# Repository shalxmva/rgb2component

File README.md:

# rgb2component
Cheap RGB to component transcoder based on dekkit schemati  https://github.com/dekkit/RGB-to-Component-Transcoder

   -The main goal for this project is to build a tiny board.
   -Next revisions will replace through hole for smd components

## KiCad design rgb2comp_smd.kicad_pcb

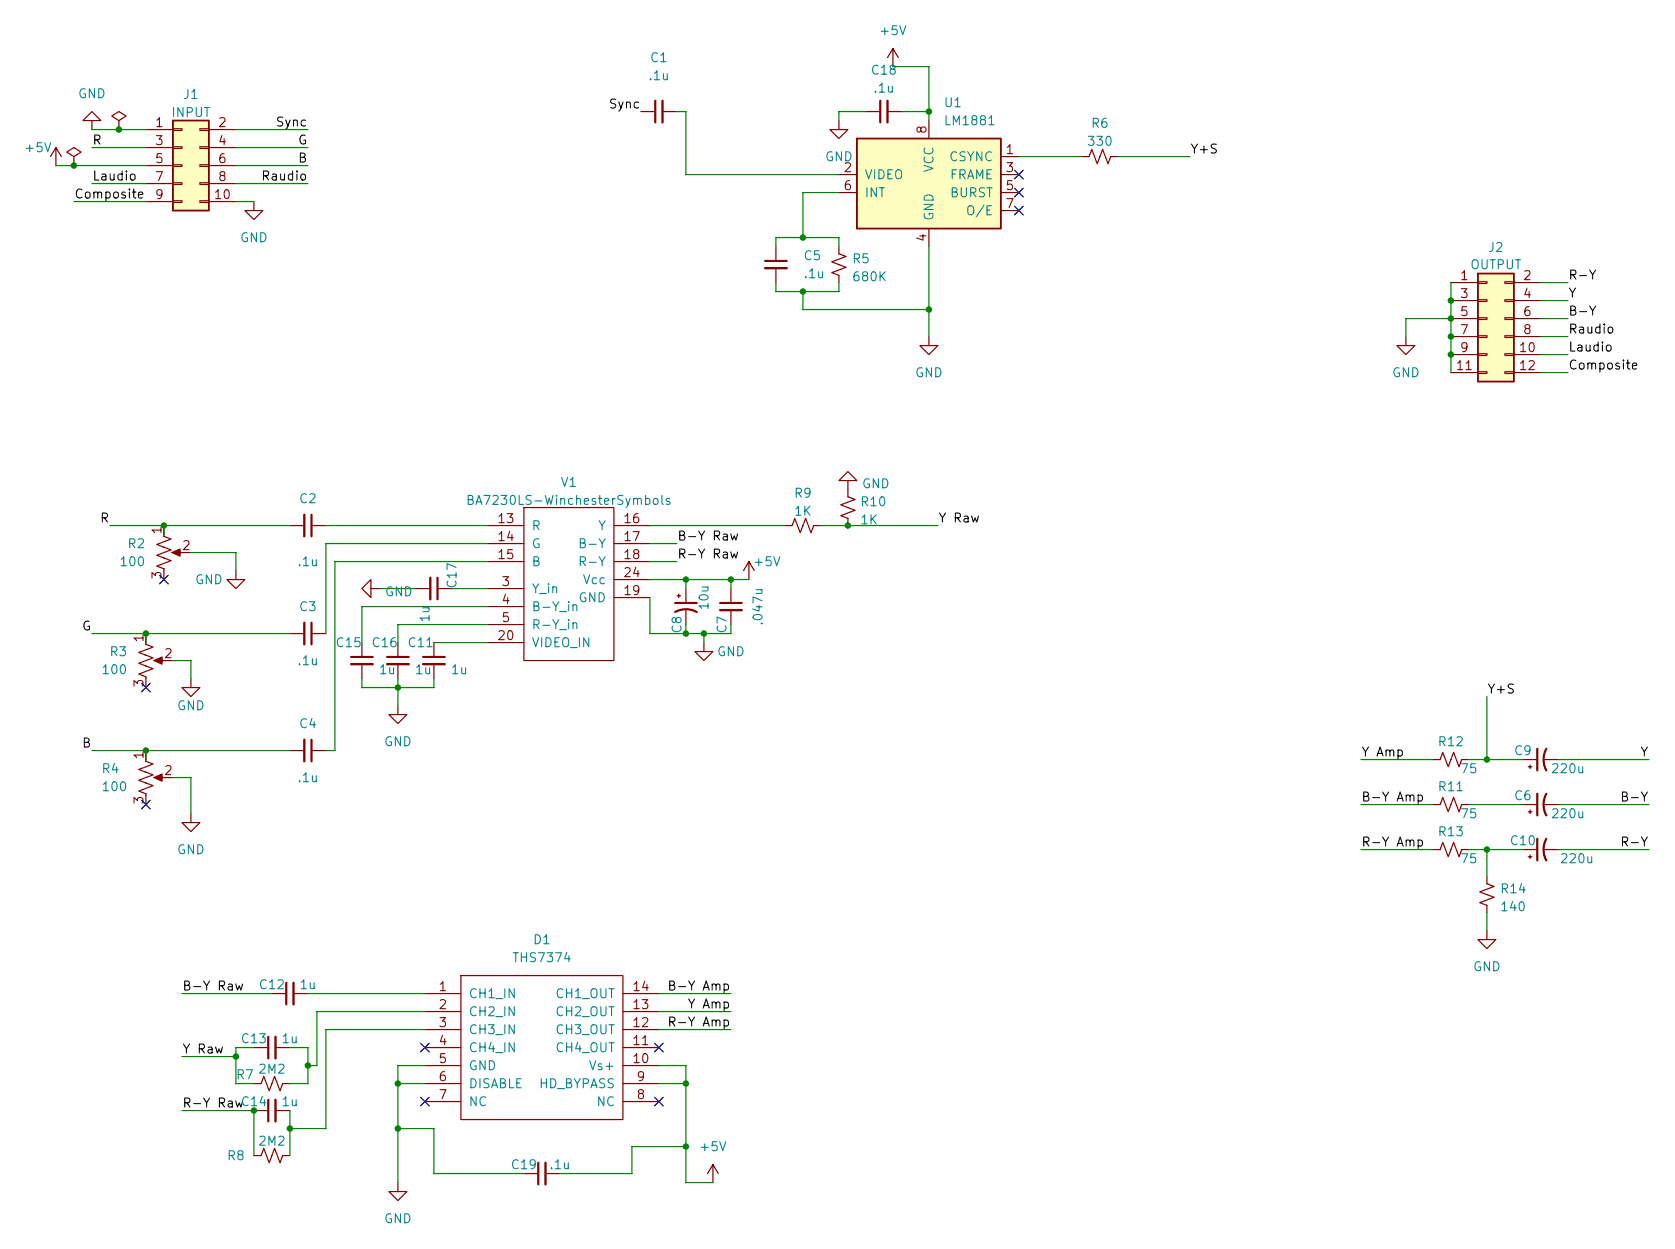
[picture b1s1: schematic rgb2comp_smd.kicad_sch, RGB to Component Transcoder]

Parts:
C1, C2, C3, C4, C5, C18, C19: .1u; C_0805_2012Metric_Pad1.18x1.45mm_HandSolder
C6, C9, C10: 220u; CP_Elec_6.3x5.4
C7: .047u; C_0805_2012Metric_Pad1.18x1.45mm_HandSolder
C8: 10u; CP_Elec_4x5.4
C11, C12, C13, C14, C15, C16, C17: 1u; C_0805_2012Metric_Pad1.18x1.45mm_HandSolder
D1: THS7374; TSSOP-14_4.4x5mm_P0.65mm
J1: INPUT; PinHeader_2x05_P2.54mm_Vertical
J2: OUTPUT; PinHeader_2x06_P2.54mm_Vertical
R2, R3, R4: 100; EVM3ESX50B
R5: 680K; R_0805_2012Metric_Pad1.20x1.40mm_HandSolder
R6: 330; R_0805_2012Metric_Pad1.20x1.40mm_HandSolder
R7, R8: 2M2; R_0805_2012Metric_Pad1.20x1.40mm_HandSolder
R9, R10: 1K; R_0805_2012Metric_Pad1.20x1.40mm_HandSolder
R11, R12, R13: 75; R_0805_2012Metric_Pad1.20x1.40mm_HandSolder
R14: 140; R_0805_2012Metric_Pad1.20x1.40mm_HandSolder
U1: LM1881; SO-8_3.9x4.9mm_P1.27mm
V1: BA7230LS-WinchesterSymbols; ZIP-24

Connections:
+5V: C7.1, C8.1, C18.2, C19.2, D1.9 (HD_BYPASS), D1.10 (Vs+), J1.5, U1.8 (VCC), V1.24 (Vcc)
/B: C4.2, J1.6, R4.1
/B-Y: C6.2, J2.6
/B-Y Amp: D1.14 (CH1_OUT), R11.1
/B-Y Raw: C12.1, V1.17 (B-Y)
/Composite: J1.9, J2.12
/G: C3.2, J1.4, R3.1
/Laudio: J1.7, J2.10
/R: C2.2, J1.3, R2.1
/R-Y: C10.2, J2.2
/R-Y Amp: D1.12 (CH3_OUT), R13.1
/R-Y Raw: C14.1, R8.1, V1.18 (R-Y)
/Raudio: J1.8, J2.8
/Sync: C1.1, J1.2
/Y: C9.2, J2.4
/Y Amp: D1.13 (CH2_OUT), R12.2
/Y Raw: C13.1, R7.1, R9.2, R10.1
/Y+S: C9.1, R6.2, R12.1
GND: C5.2, C7.2, C8.2, C11.2, C15.2, C16.2, C17.2, C18.1, C19.1, D1.5 (GND), D1.6 (DISABLE), J1.1, J1.10, J2.1, J2.3, J2.5, J2.7, J2.9, J2.11, R2.2, R3.2, R4.2, R5.1, R10.2, R14.1, U1.4 (GND), V1.19 (GND)
unnamed: C6.1, R11.2
unnamed: C10.1, R13.2, R14.2
unnamed: C12.2, D1.1 (CH1_IN)
unnamed: C13.2, D1.2 (CH2_IN), R7.2
unnamed: C14.2, D1.3 (CH3_IN), R8.2
unnamed: R6.1, U1.1 (CSYNC)
unnamed: C5.1, R5.2, U1.6 (INT)
unnamed: C1.2, U1.2 (VIDEO)
unnamed: C4.1, V1.15 (B)
unnamed: C15.1, V1.4 (B-Y_in)
unnamed: C3.1, V1.14 (G)
unnamed: C2.1, V1.13 (R)
unnamed: C16.1, V1.5 (R-Y_in)
unnamed: C11.1, V1.20 (VIDEO_IN)
unnamed: R9.1, V1.16 (Y)
unnamed: C17.1, V1.3 (Y_in)

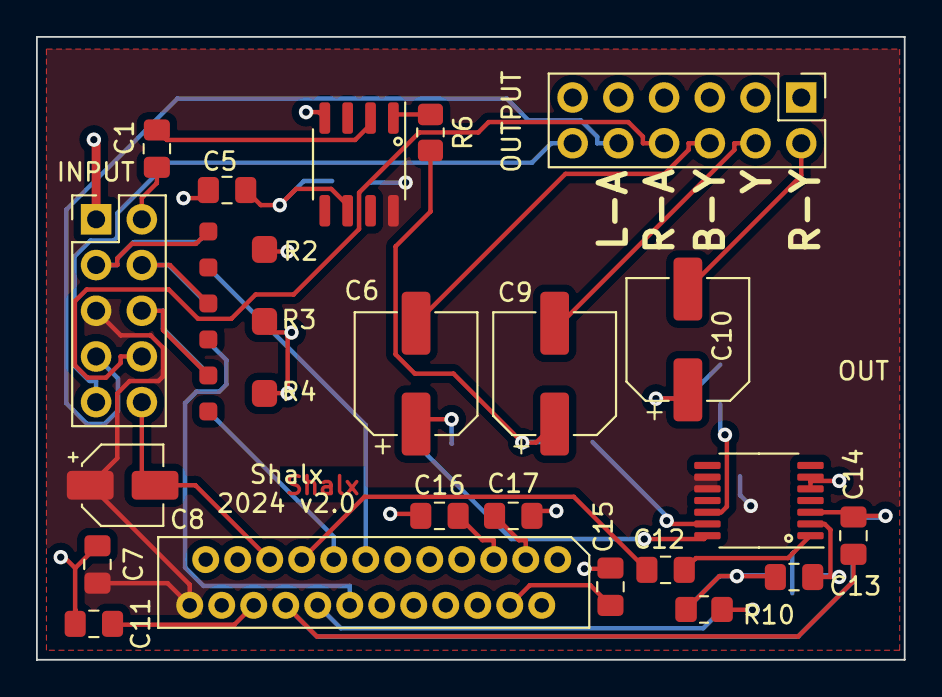
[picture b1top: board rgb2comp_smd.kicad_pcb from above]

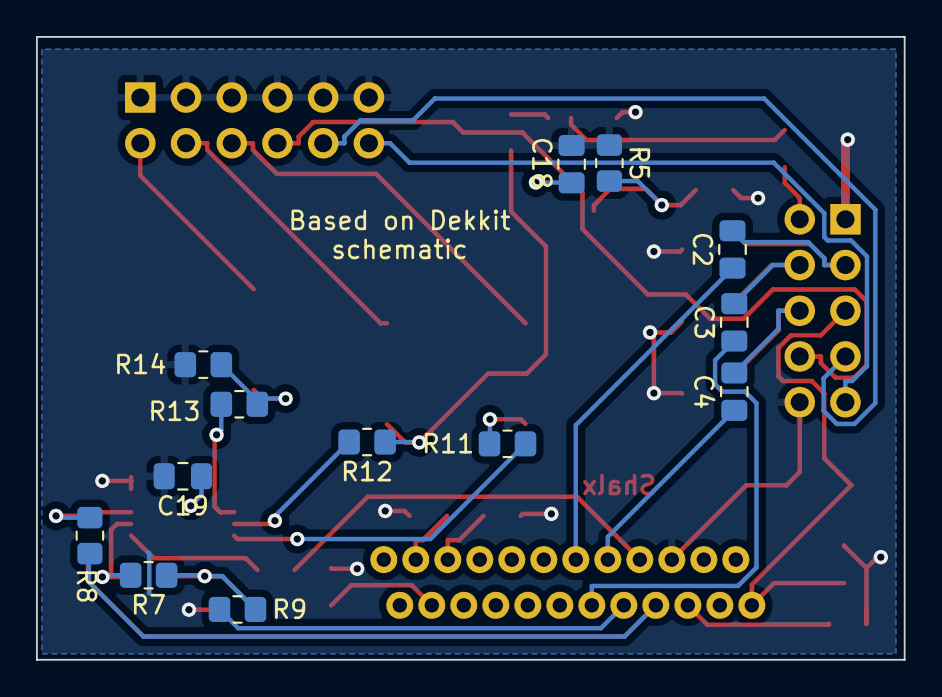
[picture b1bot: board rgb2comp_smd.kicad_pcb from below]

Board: 2 copper layers, 48.2 x 34.6 mm, 37 parts (13 on the bottom side), 35 nets.

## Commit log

2024-03-26 First board revision. TODO: Add SMD Pots
2024-03-26 Update README.md
    Adding PCB Picture
2024-04-29 Added SMD pcb version
